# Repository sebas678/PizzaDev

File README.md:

# PizzaDev
Circuito de prueba para una tarjeta de desarrollo basada en un attiny85

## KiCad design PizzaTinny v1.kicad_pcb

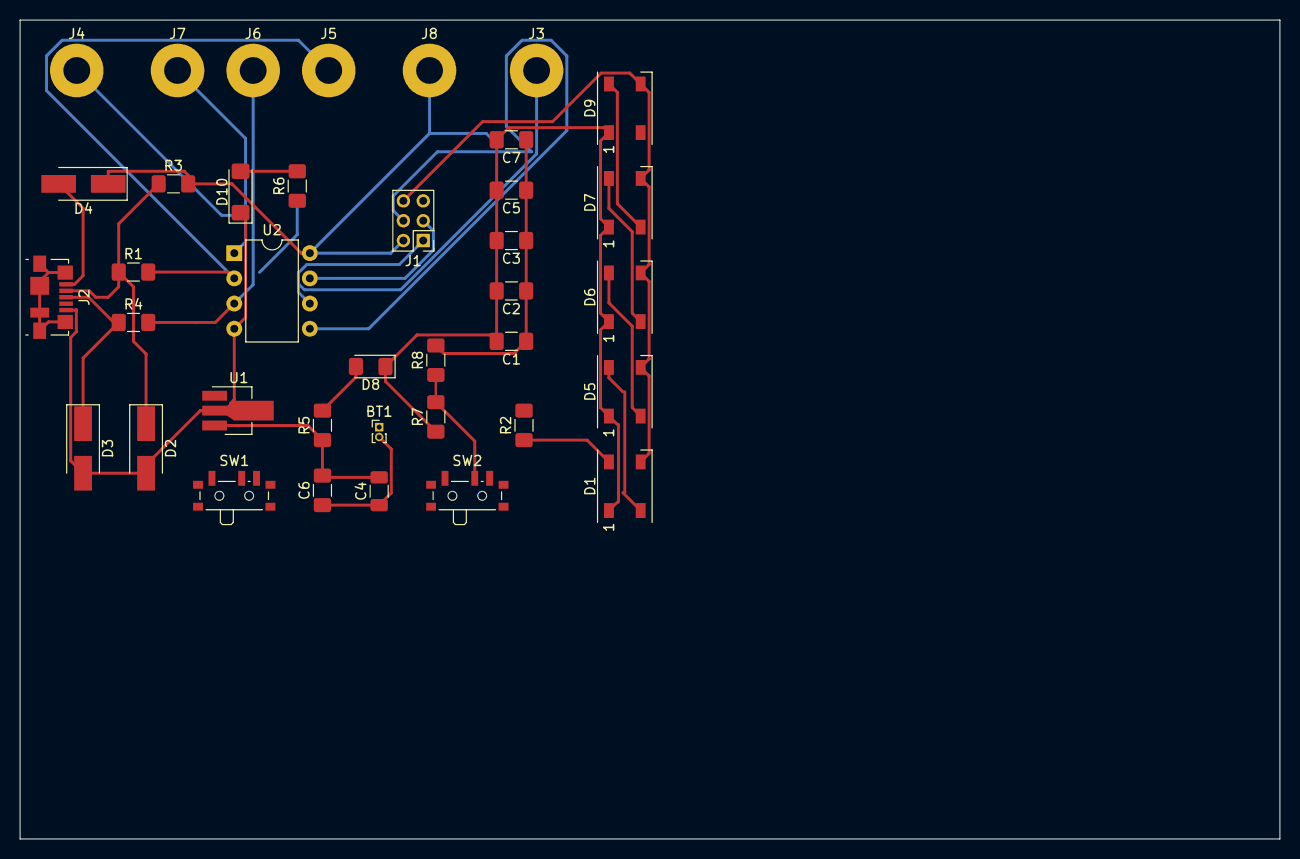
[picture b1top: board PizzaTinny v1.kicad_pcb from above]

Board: 2 copper layers, 127.0 x 82.6 mm, 38 parts (0 on the bottom side), 22 nets.

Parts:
BT1: 9v Bat; PinHeader_1x02_P1.00mm_Vertical
C1, C2, C3, C5, C6, C7: 0.1uF; C_1206_3216Metric_Pad1.42x1.75mm_HandSolder
C4: 4.7uF; C_1206_3216Metric
D1, D5, D6, D7, D9: WS2812B; LED_WS2812B_PLCC4_5.0x5.0mm_P3.2mm
D2, D3: 3.6 Zener; D_SMA_Handsoldering
D4: 1N5819; D_SMA_Handsoldering
D8: PWR Led; LED_1206_3216Metric_Pad1.42x1.75mm_HandSolder
D10: Test Led; LED_1806_4516Metric_Pad1.57x1.80mm_HandSolder
J1: AVR/ISP; PinHeader_2x03_P2.00mm_Vertical
J2: USB Micro; USB_Micro-B_Molex_47346-0001
J3: D1; MountingHole_2.7mm_M2.5_Pad
J4: GND; MountingHole_2.7mm_M2.5_Pad
J5: 3/A3; MountingHole_2.7mm_M2.5_Pad
J6: 4/A2; MountingHole_2.7mm_M2.5_Pad
J7: 5/A0; MountingHole_2.7mm_M2.5_Pad
J8: 5v; MountingHole_2.7mm_M2.5_Pad
R1, R4: 68; R_1206_3216Metric_Pad1.42x1.75mm_HandSolder
R2: 330; R_1206_3216Metric_Pad1.42x1.75mm_HandSolder
R3: 1k5; R_1206_3216Metric_Pad1.42x1.75mm_HandSolder
R5, R6, R8: 1k; R_1206_3216Metric_Pad1.42x1.75mm_HandSolder
R7: Light; R_1206_3216Metric_Pad1.42x1.75mm_HandSolder
SW1: On/Off; SW_SPDT_PCM12
SW2: I/O Light; SW_SPDT_PCM12
U1: L7805; SOT-89-3_Handsoldering
U2: ATtiny85-20PU; DIP-8_W7.62mm

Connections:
+5V: C1.2, C2.2, C3.2, C5.2, C7.2, D1.1, D4.1, D5.1, D6.1, D7.1, D8.1, D9.1, J1.2, J8.1, R3.2, R7.1, U2.8
D+: J6.1, R4.2, U2.3
D-: J5.1, R1.2, U2.2
GND: BT1.2, C1.1, C2.1, C3.1, C4.1, C5.1, C6.1, C7.1, D1.3, D2.2, D3.2, D5.3, D6.3, D7.3, D9.3, D10.1, J1.6, J2.5, J4.1, R8.2, U1.2, U2.4
Led: J1.1, J3.1, R6.1, U2.6
NeoPixel: J1.4, R2.2, U2.5
unnamed: BT1.1, SW1.1
unnamed: C4.2, C6.2, R5.1, U1.3
unnamed: D1.2, D5.4
unnamed: D1.4, R2.1
unnamed: D2.1, J2.2, R1.1, R3.1
unnamed: D3.1, J2.3, R4.1
unnamed: D4.2, J2.1
unnamed: D5.2, D6.4
unnamed: D6.2, D7.4
unnamed: D7.2, D9.4
unnamed: D8.2, R5.2
unnamed: D10.2, R6.2
unnamed: R7.2, R8.1, SW2.2
unnamed: SW1.2, U1.1
RST: J1.5, J7.1, U2.1
Sensor: J1.3, SW2.1, U2.7

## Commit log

2020-12-10 Add files via upload
    Intento #1
    Errores en los capacitores.
    Revisar la comunicación con el USB
